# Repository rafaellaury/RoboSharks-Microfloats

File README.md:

# RoboSharks - MicroFloats

Welcome to the Team RoboSharks MicroFloats Github page. I hope you enjoy your stay!

MicroFloats is a project that aims to develop a swarm of autonomous underwater vehicles for ocean exploration. The current mission it is being developed for is the discovery of larval dispersion. Scientists in Stellwagen Bank, MA are researching this unknown phenomena, and the MicroFloats will greatly aid this scientific discovery effort.

MicroFloats is an ongoing project at Georgia Tech and has had several iterations of Senior Design teams and VIP teams working on it, hence the somewhat disorganized and multilayered structure. The VIP team has a helpful wiki that helps to explain some of the electronics and BMS specifics (link [here](https://github.gatech.edu/mwoodward6/LagrangianProfiler/wiki)!)

Check out our [website](https://eceseniordesign2022spring.ece.gatech.edu/sd22p17/) for more documentation and information about the project! The details of the github are explained below.

## CAD Models

This folder contains all of the CAD models in .SLDPRT format, and were created in SolidWorks. Details on measurements can be found in the fabrication package on our website.

## MatLab Simulations

This folder contains MatLab simulations done for the Power subsystem and antenna range. These give rough metrics for how the MicrFloat will perform since we were not able to test it in full operation.

## PCB

The PCB folder contains three subfolders, one for the Battery Management System (BMS), one for the Sensor Board, and one for the Contorl Board. These all have the most up to date KiCAD PCB schematics and board layouts in there. They also include the latest Gerber and Drill files for assembly, but it is RECOMMENDED to run a DRC again before using these pregenerated files...maybe we missed something!

## Test Code

This folder contains all the code needed to test the MicroFloat and the Sensor board in particular. 

### MicroFloat Test Code

The Arduino test Code for the whole MicroFloat came mostly from the previous team (RUR) and was adapted for our needs. Note: these files are for use with the current electronics prototyping setup, which uses an SAMD51 Thing Plus. You will have to configure your Arduino IDE to interface with this board correctly as described [here.](https://learn.sparkfun.com/tutorials/samd51-thing-plus-hookup-guide/uf2-bootloader--drivers)

The following is the documentation on each of the methods for the MicroFloats test code, taken from RUR's documentation.

The following is a brief overview and description of each test code found in the MicroFloat-Test repository. Most of the code listed is for priming the system and making sure that enough oil is in the bellows versus the reservoir to achieve neutral buoyancy. When using the following programs to calibrate oil levels, it is recommended that the electronics are off to the side so that the cap of the reservoir can be taken off, and the oil levels can be monitored. Watching the oil levels is crucial as contracting or expanding the bellows too much could cause it to pop, and expanding the bellows beyond the amount of oil in the reservoir introduces air to the system. 

*do_nothing*

This program will do as it is called, nothing. This program was written in order to test the float underwater to check neutral buoyancy. It is necessary simply because the power switch at the top of the float needs to be screwed in (and therefore the system is powered). This program ensures that the microcontroller does not send any commands. 

*full_contract*

This program will remove all oil from the bellows and into the reservoir. This would be used if trying to readjust the timings if the oil levels in the reservoir/bellows became inconsistent. This program will run once.

*full_expand*

This program will remove all the oil from the reservoir and into the bellows. This would also be used to readjust the timings if the oil levels in the reservoir/bellows became inconsistent. This program will run once.

*half_contract*

This code will remove half of the oil from the bellows, into the reservoir. This code would be run if the bellows was fully expanded with oil, and the desired state was only half expanded with oil. In this case, the float would then be at neutral buoyancy. This program will run once.

*half_expand*

This code will add half the oil from the reservoir into the bellows. This could be run if the bellows was fully contracted and the desired state was half expanded with oil. In this case, the float would then be at neutral buoyancy. This program will run once. 

*mission*

This is code to be run in a test environment. The code assumes that the starting state is with a  half contract/half expanded bellows (neutral buoyancy). It will then sink the bottom of a pool by half contracting the bellows (resulting in no oil in the bellows). It will then expand half way and wait at the bottom of the pool. The float will then expand the bellows the rest of the way to rise, and then half contract the bellows to reach neutral buoyancy again. This program runs in a loop.

### Sensor Board Test Code

The Sensor Board testing setup is described in the Final Report. Basically, it uses an ARM mbed microcontroller (hence the mbed C++ code) to send RS-232 signals to the Sensor Board, and then reads the I2C output from the Sensor Board using an Arduino. The mbed code needs to be flashed onto the mbed, and then the computer needs to be connected to the Arduino so that the serial monitor can be read to see the I2C addresses and data. The **I2C Demo** code finds the I2C addresses that are currently responding. The other programs can be used to try to get data from the Sensor Board.

## VIP Team Files

This folder contains all the VIP files at the time of our project. This could be used, but it would be better to check on the latest status on the [VIP's actual Github page](https://github.gatech.edu/Aquabots-VIP), where they have links to various useful repositories.

Have fun!

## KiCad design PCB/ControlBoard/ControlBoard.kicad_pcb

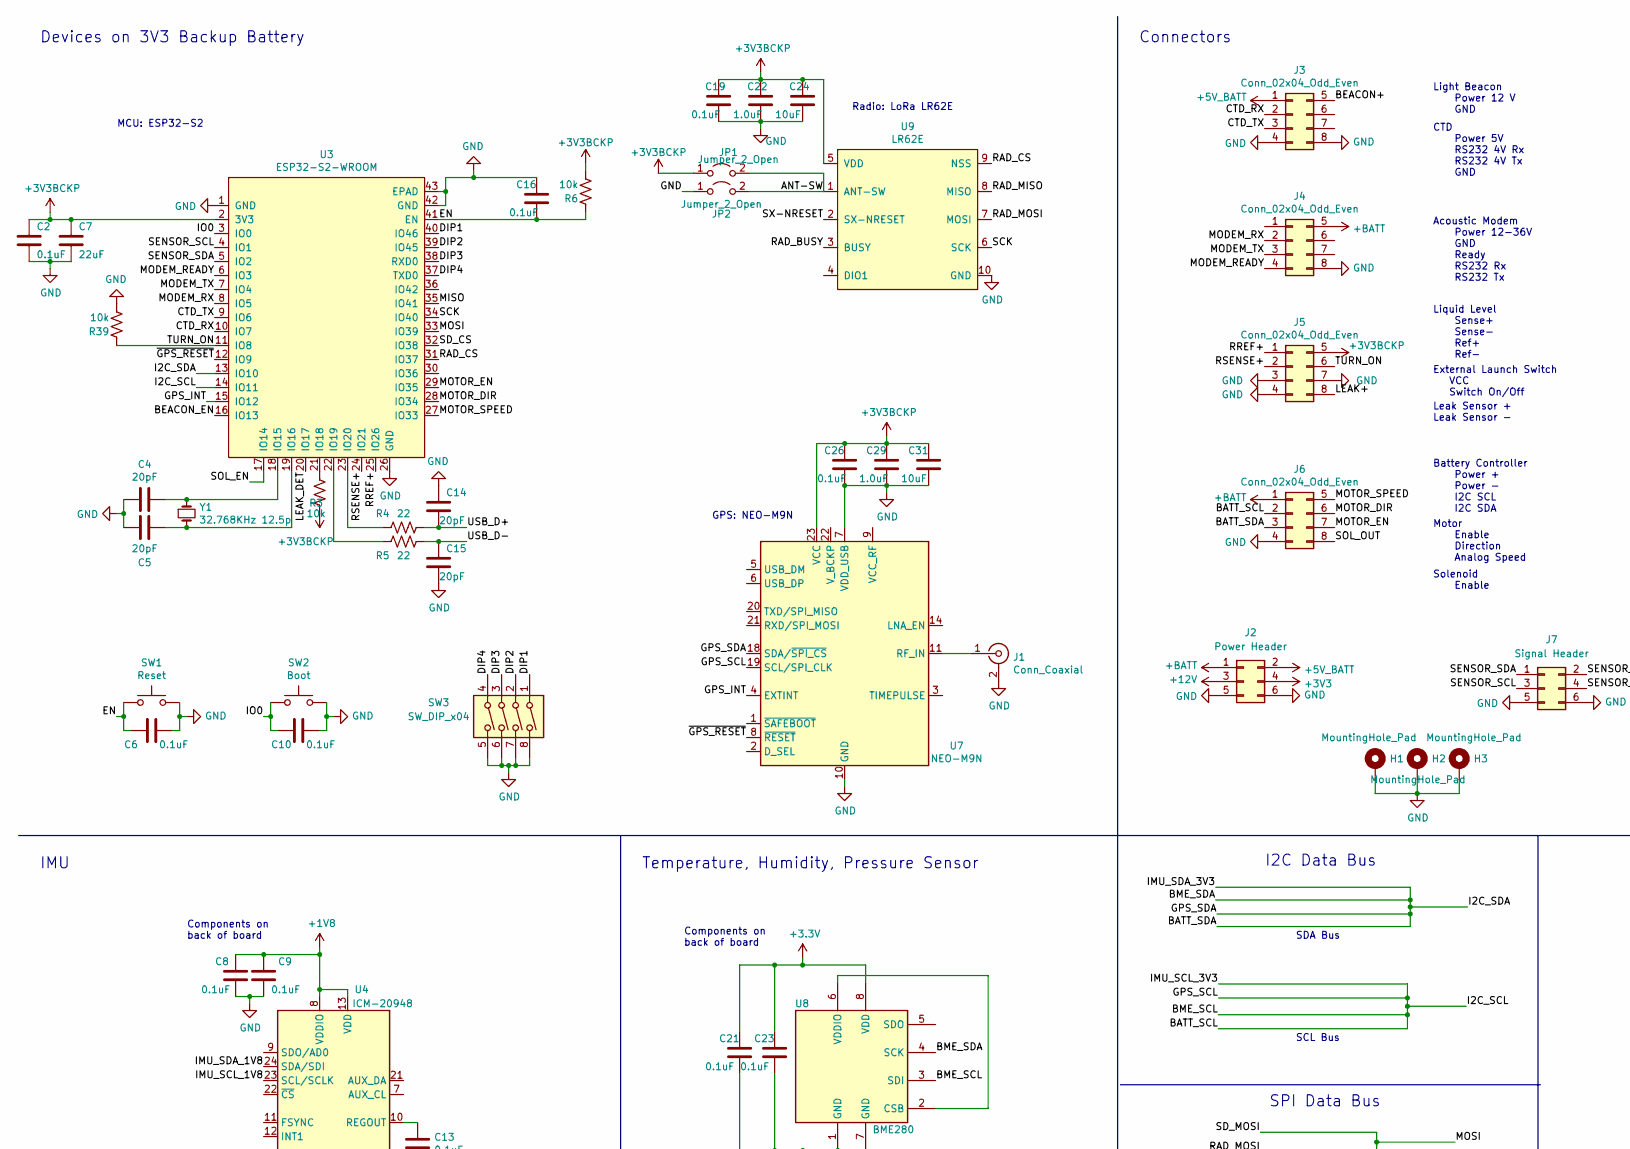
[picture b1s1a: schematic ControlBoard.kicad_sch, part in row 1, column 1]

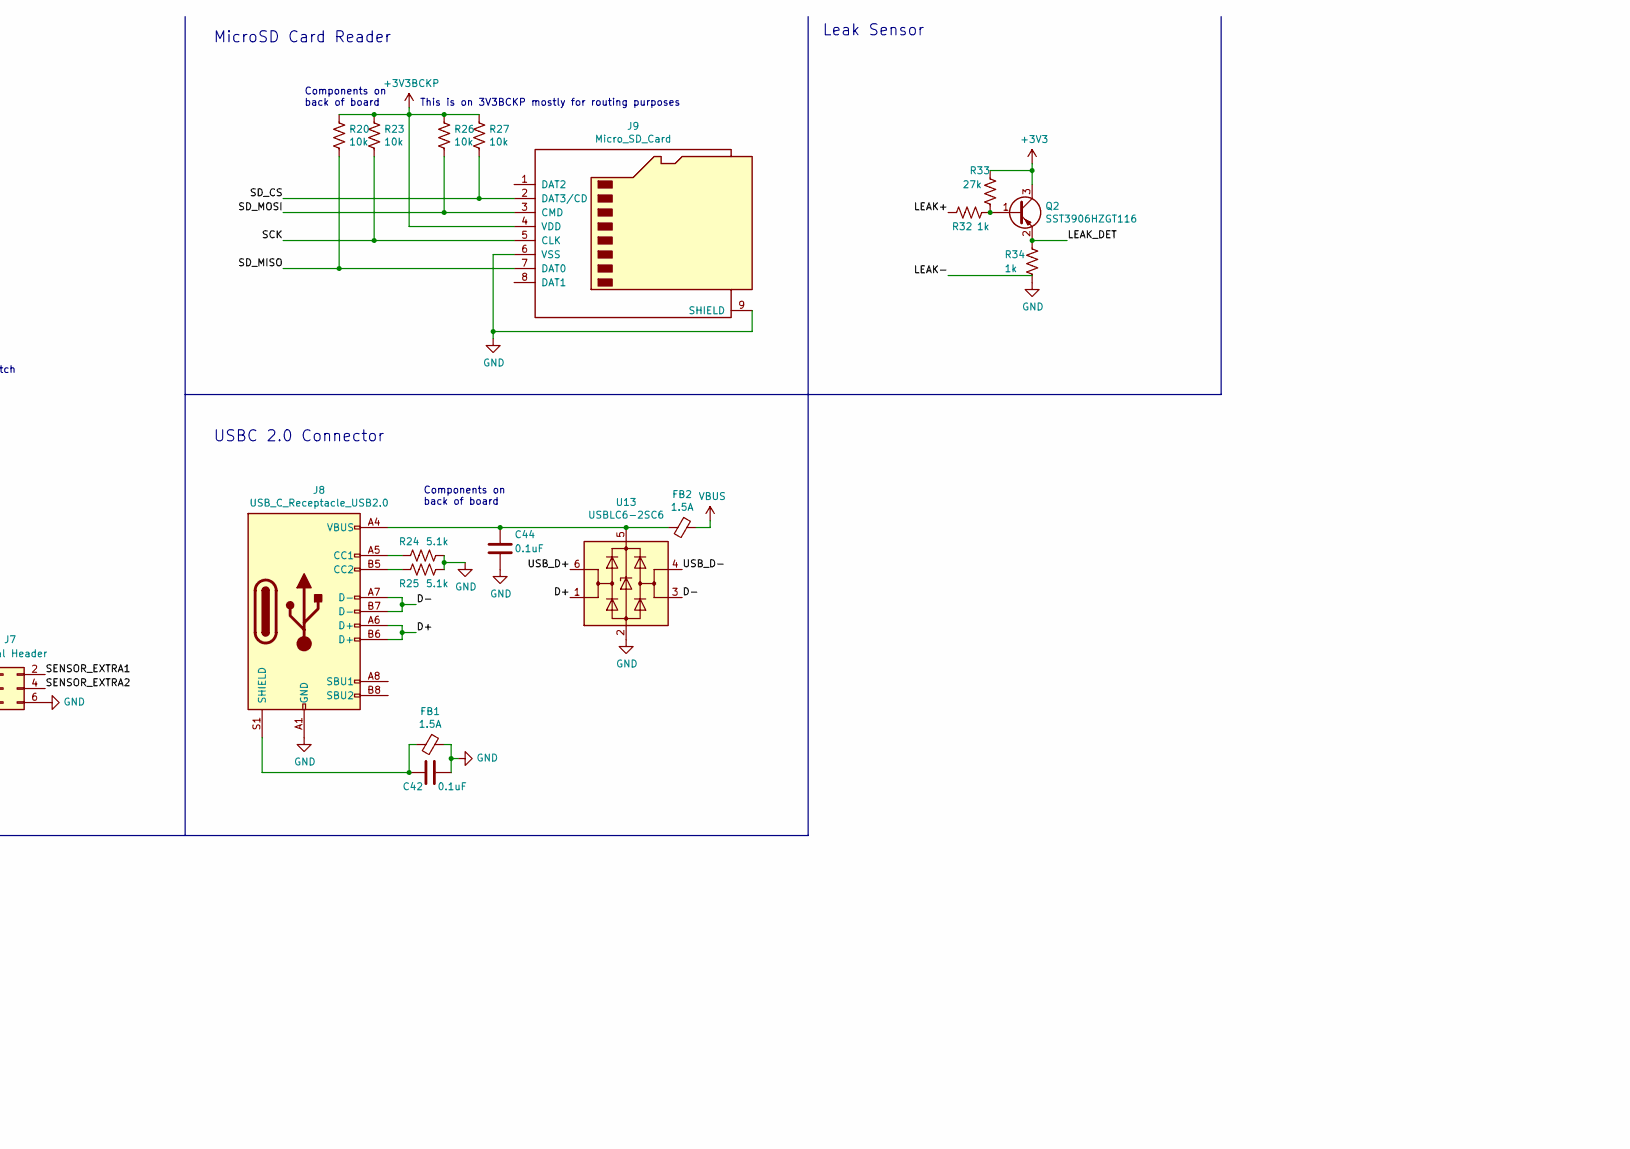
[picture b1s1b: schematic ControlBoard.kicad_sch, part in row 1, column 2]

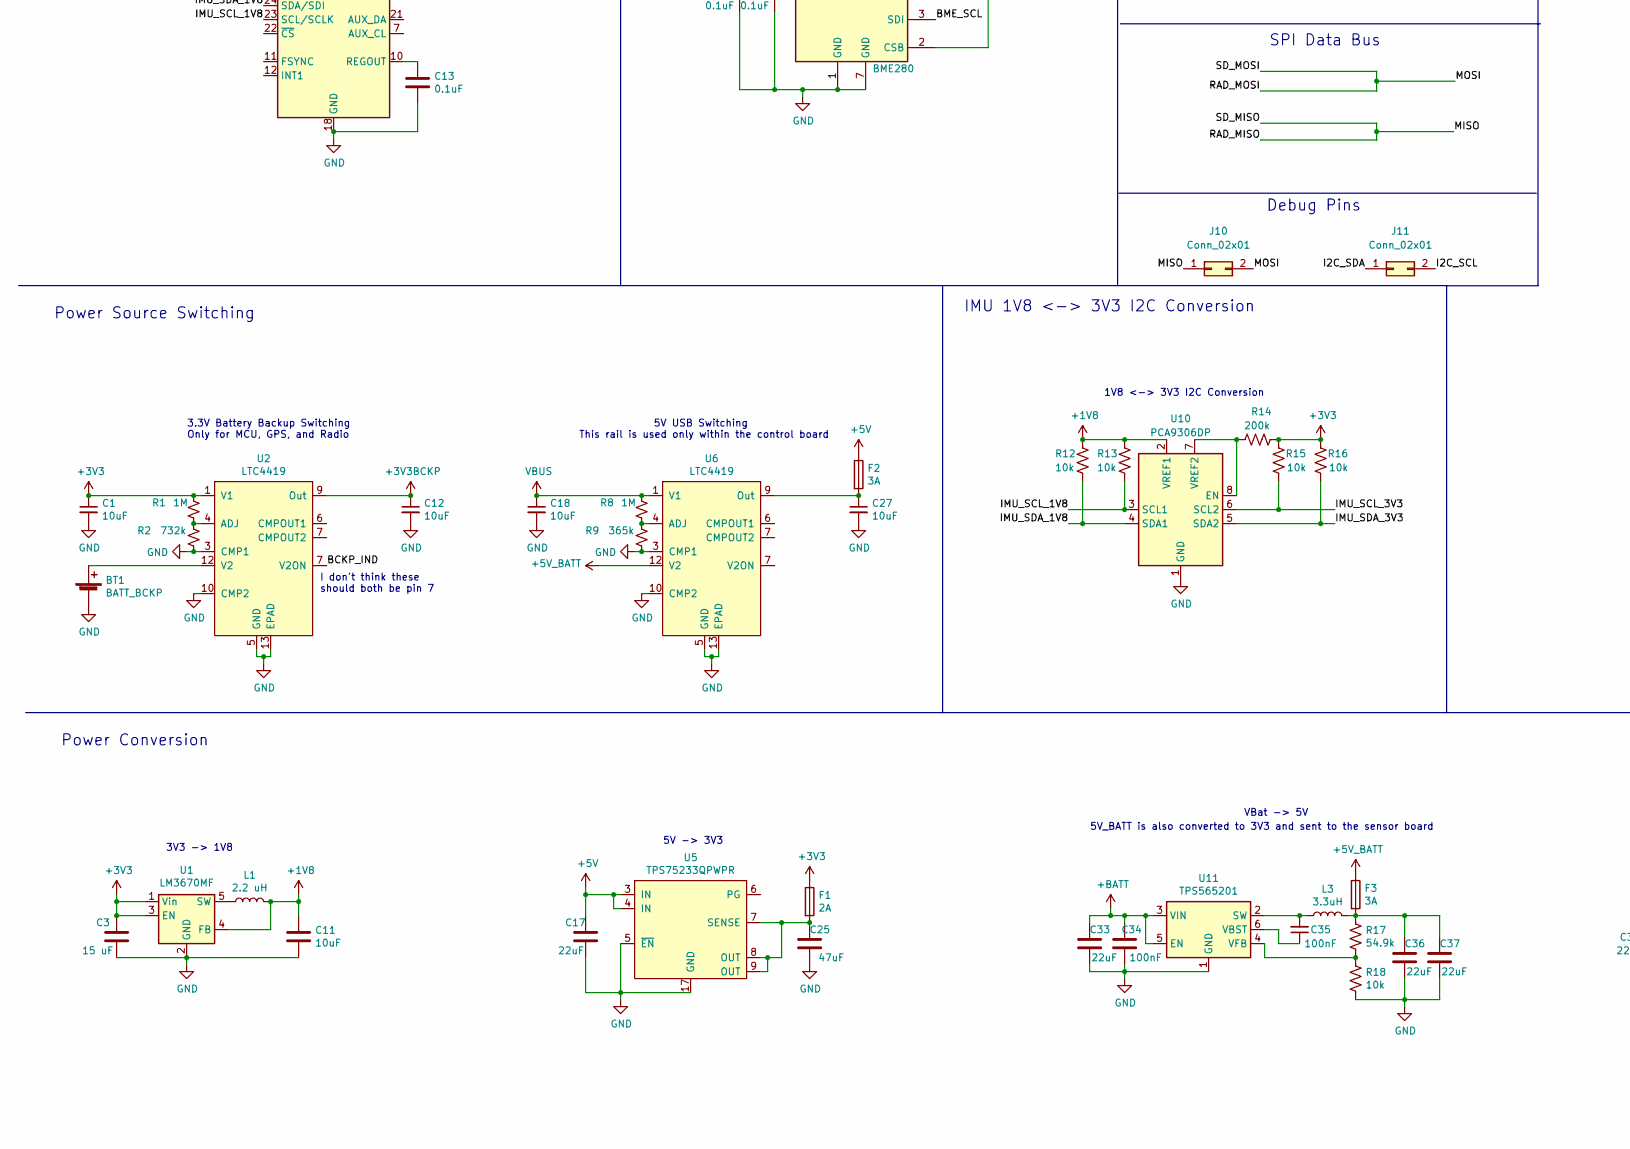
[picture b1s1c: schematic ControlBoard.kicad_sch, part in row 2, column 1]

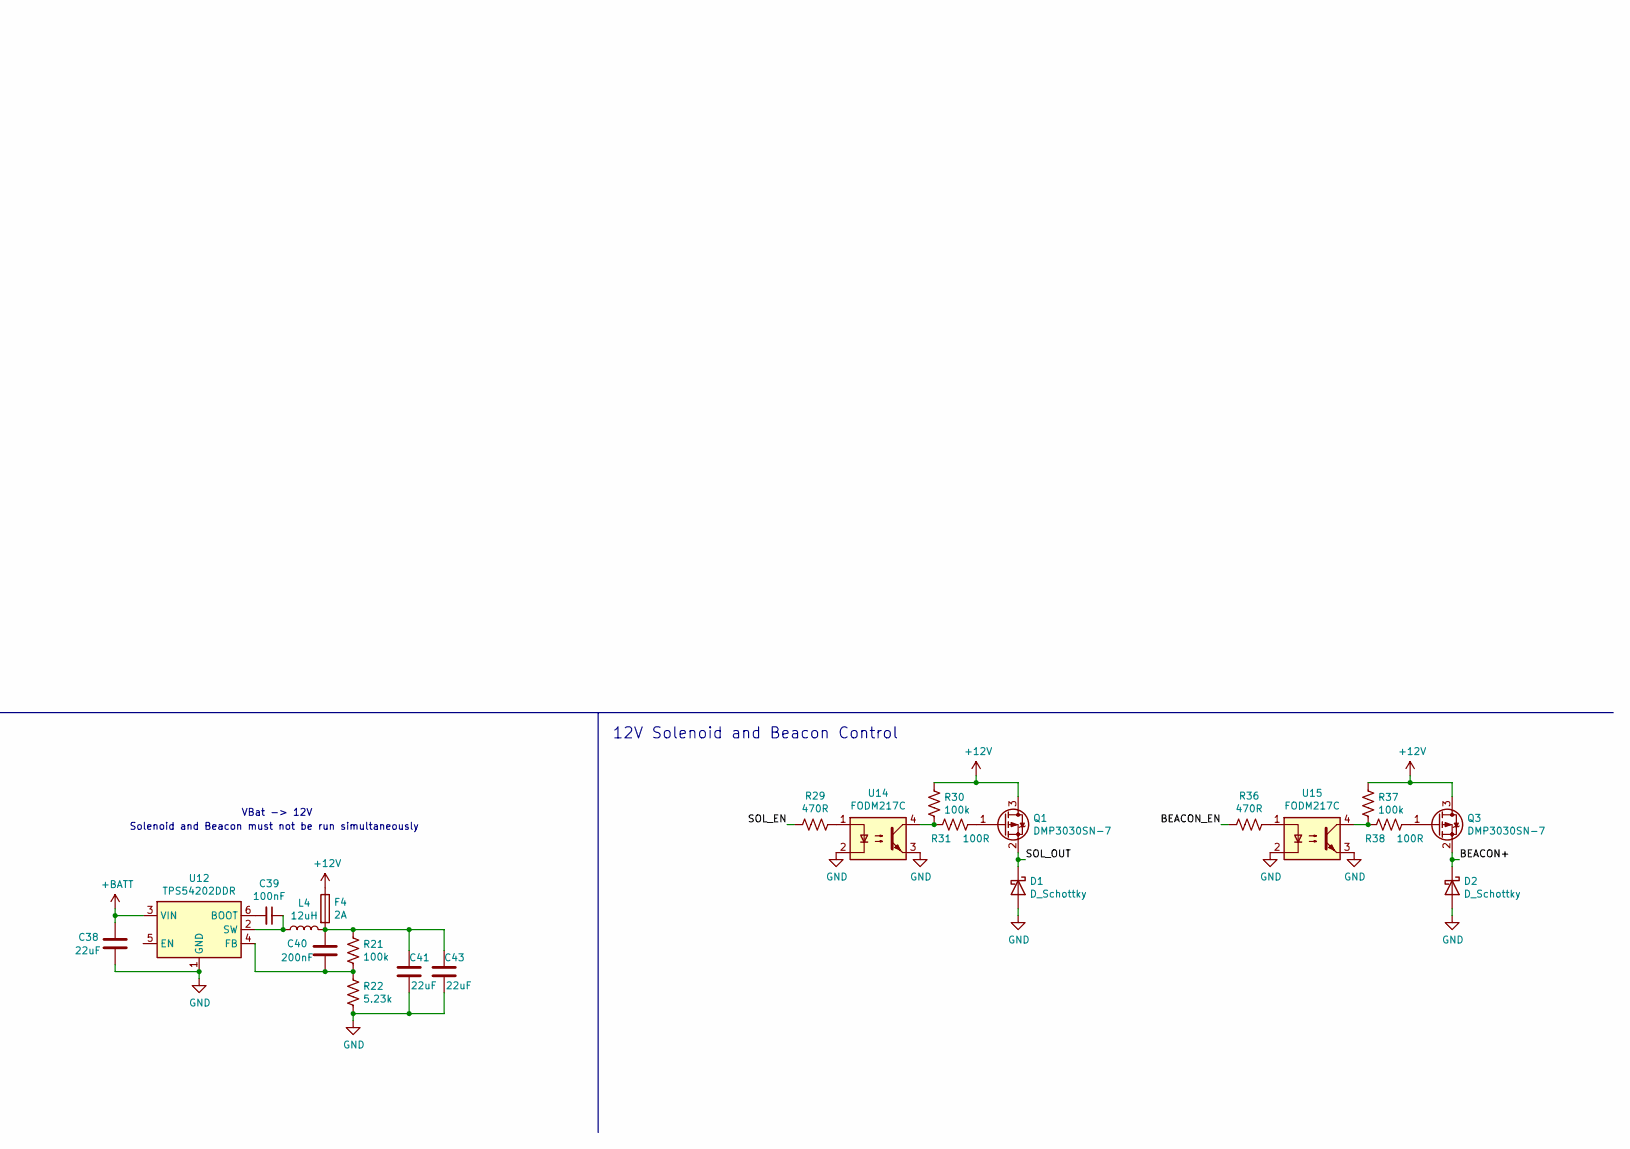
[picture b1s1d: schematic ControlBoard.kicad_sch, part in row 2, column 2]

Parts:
BT1: BATT_BCKP; BatteryHolder_Keystone_3000_1x12mm
C1, C11, C12, C18, C24, C27, C31: 10uF; C_0603_1608Metric
C2, C6, C8, C9, C10, C13, C16, C19, C21, C23, C26, C42, C44: 0.1uF; C_0603_1608Metric
C3: 15 uF; C_0603_1608Metric
C4, C5, C14, C15: 20pF; C_0603_1608Metric
C7: 22uF; C_0603_1608Metric
C17, C33, C36, C37, C38: 22uF; C_1206_3216Metric
C22, C29: 1.0uF; C_0603_1608Metric
C25: 47uF; C_1206_3216Metric
C34, C35, C39: 100nF; C_0603_1608Metric
C40: 200nF; C_0805_2012Metric
C41, C43: 22uF; CAPC6153X670N
D1, D2: D_Schottky; D_0603_1608Metric
F1, F4: 2A; Fuse_0603_1608Metric
F2, F3: 3A; Fuse_0603_1608Metric
FB1, FB2: 1.5A; L_0603_1608Metric
H1, H2, H3: MountingHole_Pad; MountingHole_3.2mm_M3_Pad_Via
J1: Conn_Coaxial; U.FL_Hirose_U.FL-R-SMT-1_Vertical
J2: Power Header; PinHeader_2x03_P2.54mm_Vertical
J3, J4, J5, J6: Conn_02x04_Odd_Even; Molex_Nano-Fit_105314-xx08_2x04_P2.50mm_Horizontal
J7: Signal Header; PinHeader_2x03_P2.54mm_Vertical
J8: USB_C_Receptacle_USB2.0; USB_C_Receptacle_HRO_TYPE-C-31-M-12
J9: Micro_SD_Card; microSD_HC_Wuerth_693072010801
J10, J11: Conn_02x01; PinHeader_2x01_P2.54mm_Vertical
JP1, JP2: Jumper_2_Open; SolderJumper-2_P1.3mm_Open_Pad1.0x1.5mm
L1: 2.2 uH; L_0805_2012Metric
L3: 3.3uH; Vishay-IHLP-3232DZ-FP_2.413x5.334-3D_4.0-0-0-MFG
L4: 12uH; L_Wuerth_WE-LQS-8040
Q1, Q3: DMP3030SN-7; SOT-23
Q2: SST3906HZGT116; SOT-23
R1, R8: 1M; R_0603_1608Metric
R2: 732k; R_0603_1608Metric
R3, R6, R12, R13, R15, R16, R18, R20, R23, R26, R27, R39: 10k; R_0603_1608Metric
R4, R5: 22; R_0603_1608Metric
R9: 365k; R_0603_1608Metric
R14: 200k; R_0603_1608Metric
R17: 54.9k; R_0603_1608Metric
R21, R30, R37: 100k; R_0603_1608Metric
R22: 5.23k; R_0603_1608Metric
R24, R25: 5.1k; R_0603_1608Metric
R29, R36: 470R; R_0603_1608Metric
R31, R38: 100R; R_0603_1608Metric
R32, R34: 1k; R_0603_1608Metric
R33: 27k; R_0603_1608Metric
SW1: Reset; SW_Push_SPST_NO_Alps_SKRK
SW2: Boot; SW_Push_SPST_NO_Alps_SKRK
SW3: SW_DIP_x04; SW_DIP_SPSTx04_Slide_6.7x11.72mm_W8.61mm_P2.54mm_LowProfile
U1: LM3670MF; TSOT-23-5
U2, U6: LTC4419; MSOP-12-1EP_3x4mm_P0.65mm_EP1.65x2.85mm_ThermalVias
U3: ESP32-S2-WROOM
U4: ICM-20948; InvenSense_QFN-24_3x3mm_P0.4mm
U5: TPS75233QPWPR; SOP65P640X110-21N
U7: NEO-M9N; ublox_NEO
U8: BME280; Bosch_LGA-8_2.5x2.5mm_P0.65mm_ClockwisePinNumbering
U9: LR62E
U10: PCA9306DP; TSSOP-8_3x3mm_P0.65mm
U11: TPS565201; SOT-23-6
U12: TPS54202DDR; SOT-23-6
U13: USBLC6-2SC6; SOT-23-6
U14, U15: FODM217C; SOP-4_4.4x2.6mm_P1.27mm
Y1: 32.768KHz 12.5p; Crystal_SMD_3215-2Pin_3.2x1.5mm

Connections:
+1V8: C8.1, C9.1, C11.1, L1.2, R12.2, R13.2, U1.4 (FB), U4.8 (VDDIO), U4.13 (VDD), U10.2 (VREF1)
+3.3BCKP: C2.1, C7.1, C12.1, C19.1, C22.1, C24.1, C26.1, C29.1, C31.1, J5.5, J9.4 (VDD), JP1.1 (A), R3.2, R6.2, R20.1, R23.1, R26.1, R27.1, U2.9 (Out), U3.2 (3V3), U7.23 (VCC), U9.5 (VDD)
+5V: C17.1, F2.1, U5.3 (IN), U5.4 (IN)
+5_BATT: F3.1, J2.2, J3.1, U6.12 (V2)
+12V: F4.1, J2.3, Q1.3 (D), Q3.3 (D), R30.1, R37.1
+BATT: C33.2, C34.2, C38.2, J2.1, J4.5, J6.1, U11.3 (VIN), U11.5 (EN), U12.3 (VIN)
/ANT-SW: JP1.2 (B), JP2.2 (B), U9.1 (ANT-SW)
/BATT_SCL: J6.2, J11.2, R15.2, U3.14 (IO11), U7.19 (SCL/SPI_CLK), U8.3 (SDI), U10.6 (SCL2)
/BATT_SDA: J6.3, J11.1, R16.2, U3.13 (IO10), U7.18 (SDA/~SPI_CS), U8.4 (SCK), U10.5 (SDA2)
/BCKP_IND: U2.7 (V2ON)
/BEACON+: D2.1 (K), J3.5, Q3.2 (S)
/BEACON_EN: R36.2, U3.16 (IO13)
/CTD_RX: J3.2, U3.10 (IO7)
/CTD_TX: J3.3, U3.9 (IO6)
/D+: J8.A6 (D+), J8.B6 (D+), U13.1 (I/O1)
/D-: J8.A7 (D-), J8.B7 (D-), U13.3 (I/O2)
/DIP1: SW3.1, U3.40 (IO46)
/DIP2: SW3.2, U3.39 (IO45)
/DIP3: SW3.3, U3.38 (RXD0)
/DIP4: SW3.4, U3.37 (TXD0)
/EN: C6.2, C16.2, R6.1, SW1.1, U3.41 (EN)
/GPS_INT: U3.15 (IO12), U7.4 (EXTINT)
/IMU_SCL_1V8: R13.1, U4.23 (SCL/SCLK), U10.3 (SCL1)
/IMU_SDA_1V8: R12.1, U4.24 (SDA/SDI), U10.4 (SDA1)
/IO0: C10.2, SW2.1, U3.3 (IO0)
/LEAK+: J5.8, R32.2
/LEAK_DET: Q2.2 (E), R34.2, U3.20 (IO17)
/MISO: J9.7 (DAT0), J10.1, R20.2, U3.35 (IO41), U9.8 (MISO)
/MODEM_READY: J4.4, U3.6 (IO3)
/MODEM_RX: J4.2, U3.8 (IO5)
/MODEM_TX: J4.3, U3.7 (IO4)
/MOSI: J9.3 (CMD), J10.2, R26.2, U3.33 (IO39), U9.7 (MOSI)
/MOTOR_DIR: J6.6, U3.28 (IO34)
/MOTOR_EN: J6.7, U3.29 (IO35)
/MOTOR_SPEED: J6.5, U3.27 (IO33)
/RAD_BUSY: U9.3 (BUSY)
/RAD_CS: U3.31 (IO37), U9.9 (NSS)
/RREF+: J5.1, U3.25 (IO26)
/RSENSE+: J5.2, U3.24 (IO21)
/SCK: J9.5 (CLK), R23.2, U3.34 (IO40), U9.6 (SCK)
/SD_CS: J9.2 (DAT3/CD), R27.2, U3.32 (IO38)
/SENSOR_EXTRA1: J7.2
/SENSOR_EXTRA2: J7.4
/SENSOR_SCL: J7.3, U3.4 (IO1)
/SENSOR_SDA: J7.1, U3.5 (IO2)
/SOL_EN: R29.2, U3.17 (IO14)
/SOL_OUT: D1.1 (K), J6.8, Q1.2 (S)
/SX-NRESET: U9.2 (SX-NRESET)
/TURN_ON: J5.6, R39.1, U3.11 (IO8)
/USB_D+: C14.2, R4.2, U13.6 (I/O1)
/USB_D-: C15.1, R5.2, U13.4 (I/O2)
/~GPS_RESET: U3.12 (IO9), U7.8 (~RESET)
GND: BT1.2 (-), C1.2, C2.2, C3.1, C4.2, C5.1, C6.1, C7.2, C8.2, C9.2, C10.1, C11.2, C12.2, C13.2, C14.1, C15.2, C16.1, C17.2, C18.2, C19.2, C21.2, C22.2, C23.2, C24.2, C25.1, C26.2, C27.2, C29.2, C31.2, C33.1, C34.1, C36.1, C37.1, C38.1, C41.1, C42.1, C43.1, C44.2, D1.2 (A), D2.2 (A), FB1.1, H1.1, H2.1, H3.1, J1.2 (Ext), J2.5, J2.6, J3.4, J3.8, J4.8, J5.3, J5.4, J5.7, J6.4, J7.5, J7.6, J8.A1 (GND), J8.A12 (GND), J8.B1 (GND), J8.B12 (GND), J9.6 (VSS), J9.9 (SHIELD), JP2.1 (A), R2.1, R9.1, R18.1, R22.1, R24.2, R25.1, R34.1, R39.2, SW1.2, SW2.2, SW3.5, SW3.6, SW3.7, SW3.8, U1.2 (GND), U2.3 (CMP1), U2.5 (GND), U2.10 (CMP2), U2.13 (EPAD), U3.1 (GND), U3.26 (GND), U3.42 (GND), U3.43 (EPAD), U4.18 (GND), U4.20 (GND), U5.5 (~EN), U5.17 (GND), U6.3 (CMP1), U6.5 (GND), U6.10 (CMP2), U6.13 (EPAD), U7.7 (VDD_USB), U7.10 (GND), U7.12 (GND), U7.13 (GND), U7.24 (GND), U8.1 (GND), U8.7 (GND), U9.10 (GND), U10.1 (GND), U11.1 (GND), U12.1 (GND), U13.2 (GND), U14.2, U14.3, U15.2, U15.3
unnamed: BT1.1 (+), U2.12 (V2)
unnamed: C4.1, U3.18 (IO15), Y1.1
unnamed: C5.2, U3.19 (IO16), Y1.2
unnamed: C13.1, U4.10 (REGOUT)
unnamed: C25.2, F1.2, U5.7 (SENSE), U5.8 (OUT), U5.9 (OUT)
unnamed: C27.1, F2.2, U6.9 (Out)
unnamed: C35.1, U11.6 (VBST)
unnamed: C35.2, L3.1, U11.2 (SW)
unnamed: C36.2, C37.2, F3.2, L3.2, R17.1
unnamed: C39.1, L4.1, U12.2 (SW)
unnamed: C39.2, U12.6 (BOOT)
unnamed: C40.1, C41.2, C43.2, F4.2, L4.2, R21.1
unnamed: C40.2, R21.2, R22.2, U12.4 (FB)
unnamed: C42.2, FB1.2, J8.S1 (SHIELD)
unnamed: C44.1, FB2.2, J8.A4 (VBUS), J8.A9 (VBUS), J8.B4 (VBUS), J8.B9 (VBUS), U13.5 (VBUS)
unnamed: J1.1 (In), U7.11 (RF_IN)
unnamed: J8.A5 (CC1), R24.1
unnamed: J8.B5 (CC2), R25.2
unnamed: L1.1, U1.5 (SW)
unnamed: Q1.1 (G), R31.1
unnamed: Q2.1 (B), R32.1, R33.1
unnamed: Q3.1 (G), R38.1
unnamed: R1.2, R2.2, U2.4 (ADJ)
unnamed: R3.1, U3.21 (IO18)
unnamed: R4.1, U3.23 (IO20)
unnamed: R5.1, U3.22 (IO19)
unnamed: R8.2, R9.2, U6.4 (ADJ)
unnamed: R14.1, U10.7 (VREF2), U10.8 (EN)
unnamed: R17.2, R18.2, U11.4 (VFB)
unnamed: R29.1, U14.1
unnamed: R30.2, R31.2, U14.4
unnamed: R36.1, U15.1
unnamed: R37.2, R38.2, U15.4
unnamed: U8.2 (CSB), U8.6 (VDDIO)
VBUS: C18.1, FB2.1, R8.1, U6.1 (V1)

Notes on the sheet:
External Launch Switch VCC Switch On/Off
I2C Data Bus
Components on back of board
SCL Bus
Devices on 3V3 Backup Battery
USBC 2.0 Connector
Power Source Switching
I don't think these should both be pin 7
Light Beacon Power 12 V GND
Battery Controller Power + Power - I2C SCL I2C SDA
1V8 <-> 3V3 I2C Conversion
Leak Sensor
Power Conversion
Debug Pins
Connectors
Motor Enable Direction Analog Speed
Acoustic Modem Power 12-36V GND Ready RS232 Rx RS232 Tx
GPS: NEO-M9N
5V_BATT is also converted to 3V3 and sent to the sensor board
Leak Sensor + Leak Sensor -
SPI Data Bus
IMU
This is on 3V3BCKP mostly for routing purposes
Temperature, Humidity, Pressure Sensor
12V Solenoid and Beacon Control
3.3V Battery Backup Switching Only for MCU, GPS, and Radio
Solenoid Enable
Liquid Level Sense+ Sense- Ref+ Ref-
Radio: LoRa LR62E
3V3 -> 1V8
MCU: ESP32-S2
5V -> 3V3
CTD Power 5V RS232 4V Rx RS232 4V Tx GND
MicroSD Card Reader
VBat -> 12V
IMU 1V8 <-> 3V3 I2C Conversion
VBat -> 5V
Solenoid and Beacon must not be run simultaneously
5V USB Switching This rail is used only within the control board
SDA Bus

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
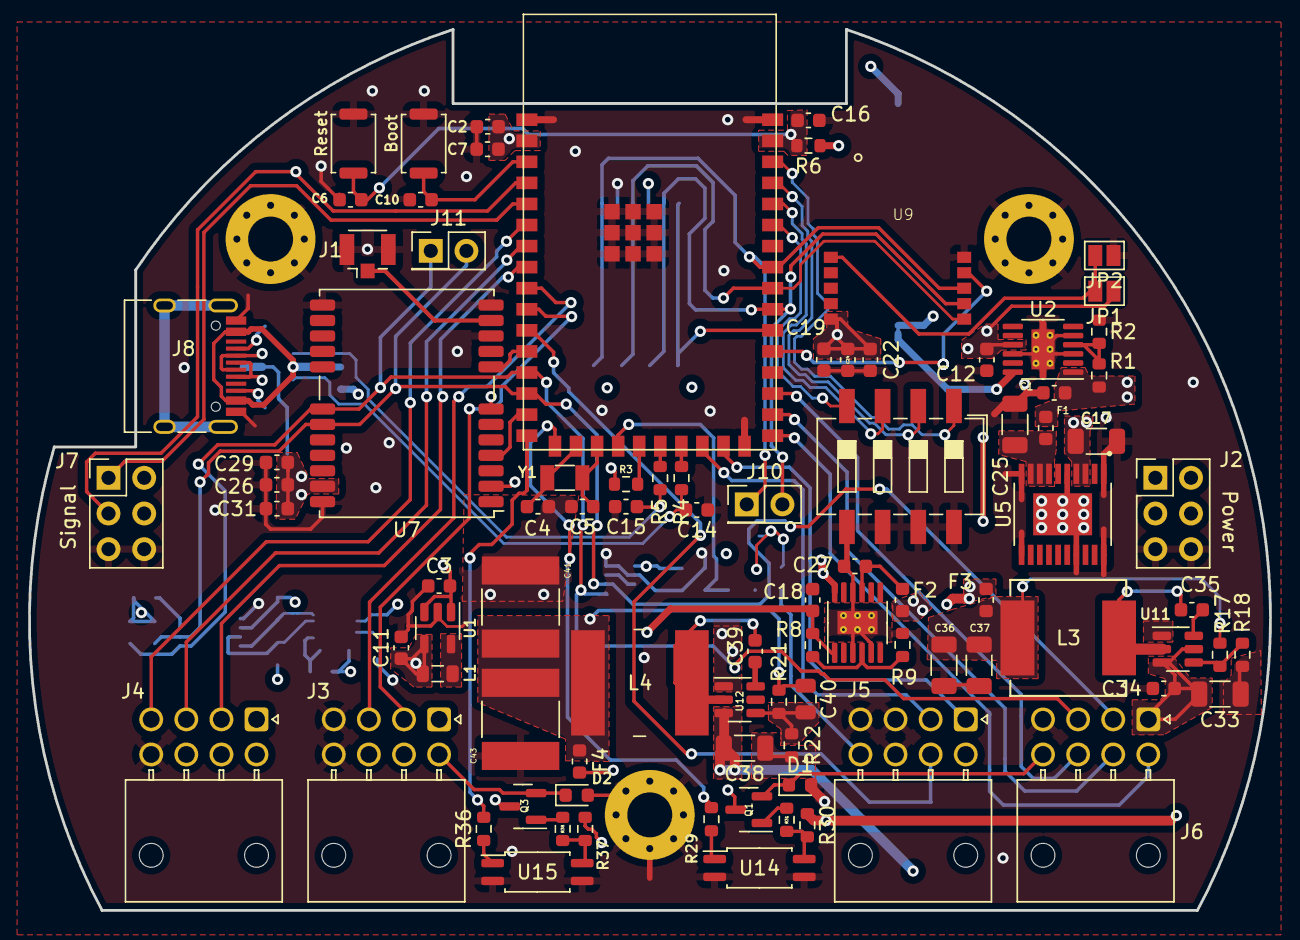
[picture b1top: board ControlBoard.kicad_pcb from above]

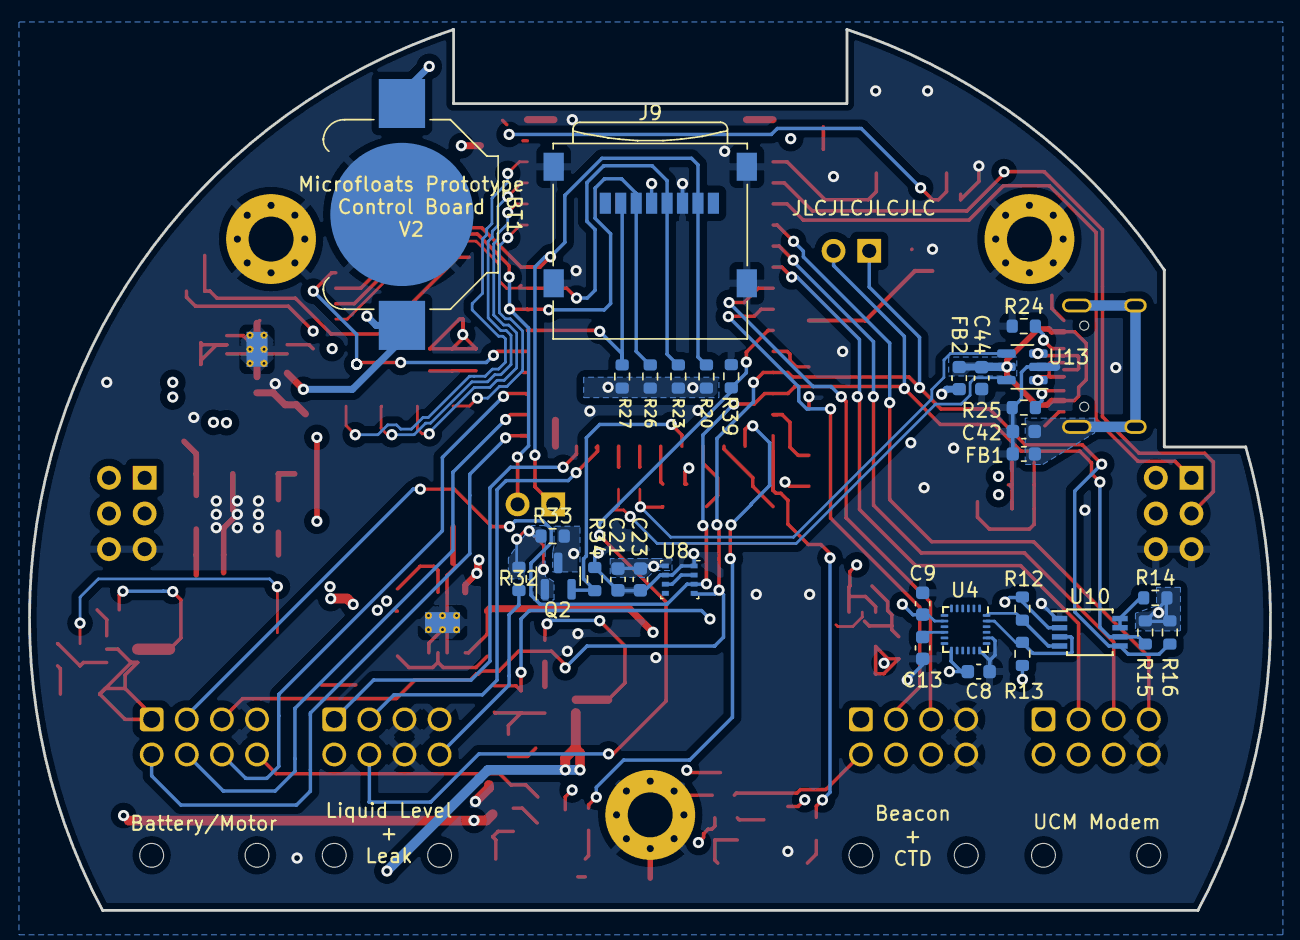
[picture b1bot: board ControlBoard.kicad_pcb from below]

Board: 4 copper layers, 88.4 x 62.7 mm, 123 parts (31 on the bottom side), 84 nets.

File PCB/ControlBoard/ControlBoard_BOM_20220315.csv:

"Id";"Designator";"Package";"Quantity";"Designation";"Supplier and ref";
1;"U5";"SOP65P640X110-21N";1;"TPS75233QPWPR";;;
2;"J8";"USB_C_Receptacle_HRO_TYPE-C-31-M-12";1;"USB_C_Receptacle_USB2.0";;;
3;"J3,J4,J5,J6";"Molex_Nano-Fit_105314-xx08_2x04_P2.50mm_Horizontal";4;"Conn_02x04_Odd_Even";;;
4;"U7";"ublox_NEO";1;"NEO-M9N";;;
5;"U3";"ESP32-S2-WROOM";1;"ESP32-S2-WROOM";;;
6;"R29,R36";"R_0603_1608Metric";2;"470R";;;
7;"U14,U15";"SOP-4_4.4x2.6mm_P1.27mm";2;"FODM217C";;;
8;"R31,R38";"R_0603_1608Metric";2;"100R";;;
9;"R30,R21,R37";"R_0603_1608Metric";3;"100k";;;
10;"Q1,Q3";"SOT-23";2;"DMP3030SN-7";;;
11;"D1,D2";"D_0603_1608Metric";2;"D_Schottky";;;
12;"J2";"PinHeader_2x03_P2.54mm_Vertical";1;"Power Header";;;
13;"J7";"PinHeader_2x03_P2.54mm_Vertical";1;"Signal Header";;;
14;"BT1";"BR-1632A_HAN";1;"BATT_BCKP";;;
15;"C1,C11,C12,C18,C24,C27,C31";"C_0603_1608Metric";7;"10uF";;;
16;"C2,C6,C8,C9,C10,C13,C16,C19,C21,C23,C26,C42,C44";"C_0603_1608Metric";13;"0.1uF";;;
17;"C3";"C_0603_1608Metric";1;"15 uF";;;
18;"C4,C5,C14,C15";"C_0603_1608Metric";4;"20pF";;;
19;"C7";"C_0603_1608Metric";1;"22uF";;;
20;"C17,C33,C36,C37,C38";"C_1206_3216Metric";5;"22uF";;;
21;"C22,C29";"C_0603_1608Metric";2;"1.0uF";;;
22;"C34,C35,C39";"C_0603_1608Metric";3;"100nF";;;
23;"C40";"C_0805_2012Metric";1;"200nF";;;
24;"C41,C43";"CAPC6153X670N";2;"22uF";;;
25;"F1,F4";"Fuse_0603_1608Metric";2;"2A";;;
26;"F2,F3";"Fuse_0603_1608Metric";2;"3A";;;
27;"FB1,FB2";"L_0603_1608Metric";2;"1.5A";;;
28;"J1";"U.FL_Hirose_U.FL-R-SMT-1_Vertical";1;"Conn_Coaxial";;;
29;"J9";"microSD_HC_Wuerth_693072010801";1;"Micro_SD_Card";;;
30;"L1";"L_0805_2012Metric";1;"2.2 uH";;;
31;"L3";"Vishay-IHLP-3232DZ-FP_2.413x5.334-3D_4.0-0-0-MFG";1;"3.3uH";;;
32;"L4";"L_Wuerth_WE-LQS-8040";1;"12uH";;;
33;"Q2";"SOT-23";1;"SST3906HZGT116";;;
34;"R1,R8";"R_0603_1608Metric";2;"1M";;;
35;"R2";"R_0603_1608Metric";1;"732k";;;
36;"R3,R6,R12,R13,R15,R16,R18,R19,R20,R23,R26,R27,R28";"R_0603_1608Metric";13;"10k";;;
37;"R4,R5";"R_0603_1608Metric";2;"22";;;
38;"R9";"R_0603_1608Metric";1;"365k";;;
39;"R14";"R_0603_1608Metric";1;"200k";;;
40;"R17";"R_0603_1608Metric";1;"54.9k";;;
41;"R22";"R_0603_1608Metric";1;"5.23k";;;
42;"R24,R25";"R_0603_1608Metric";2;"5.1k";;;
43;"R32,R34";"R_0603_1608Metric";2;"1k";;;
44;"R33";"R_0603_1608Metric";1;"27k";;;
45;"SW1";"SW_Push_SPST_NO_Alps_SKRK";1;"Reset";;;
46;"SW2";"SW_Push_SPST_NO_Alps_SKRK";1;"Boot";;;
47;"SW3";"SW_DIP_SPSTx04_Slide_6.7x11.72mm_W8.61mm_P2.54mm_LowProfile";1;"SW_DIP_x04";;;
48;"U1";"TSOT-23-5";1;"LM3670MF";;;
49;"U2,U6";"MSOP-12-1EP_3x4mm_P0.65mm_EP1.65x2.85mm_ThermalVias";2;"LTC4419";;;
50;"U4";"InvenSense_QFN-24_3x3mm_P0.4mm";1;"ICM-20948";;;
51;"U8";"Bosch_LGA-8_2.5x2.5mm_P0.65mm_ClockwisePinNumbering";1;"BME280";;;
52;"U9";"LR62E";1;"LR62E";;;
53;"U10";"TSSOP-8_3x3mm_P0.65mm";1;"PCA9306DP";;;
54;"U11";"SOT-23-6";1;"TPS565201";;;
55;"U12";"SOT-23-6";1;"TPS54202DDR";;;
56;"U13";"SOT-23-6";1;"USBLC6-2SC6";;;
57;"Y1";"Crystal_SMD_3215-2Pin_3.2x1.5mm";1;"32.768KHz 12.5p";;;
58;"C25";"C_1206_3216Metric";1;"47uF";;;

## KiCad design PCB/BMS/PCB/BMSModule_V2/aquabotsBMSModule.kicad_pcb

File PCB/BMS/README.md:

# Battery Management System
For more information please check out our [wiki](https://github.gatech.edu/Aquabots-VIP/BatteryManagementSystem/wiki)!

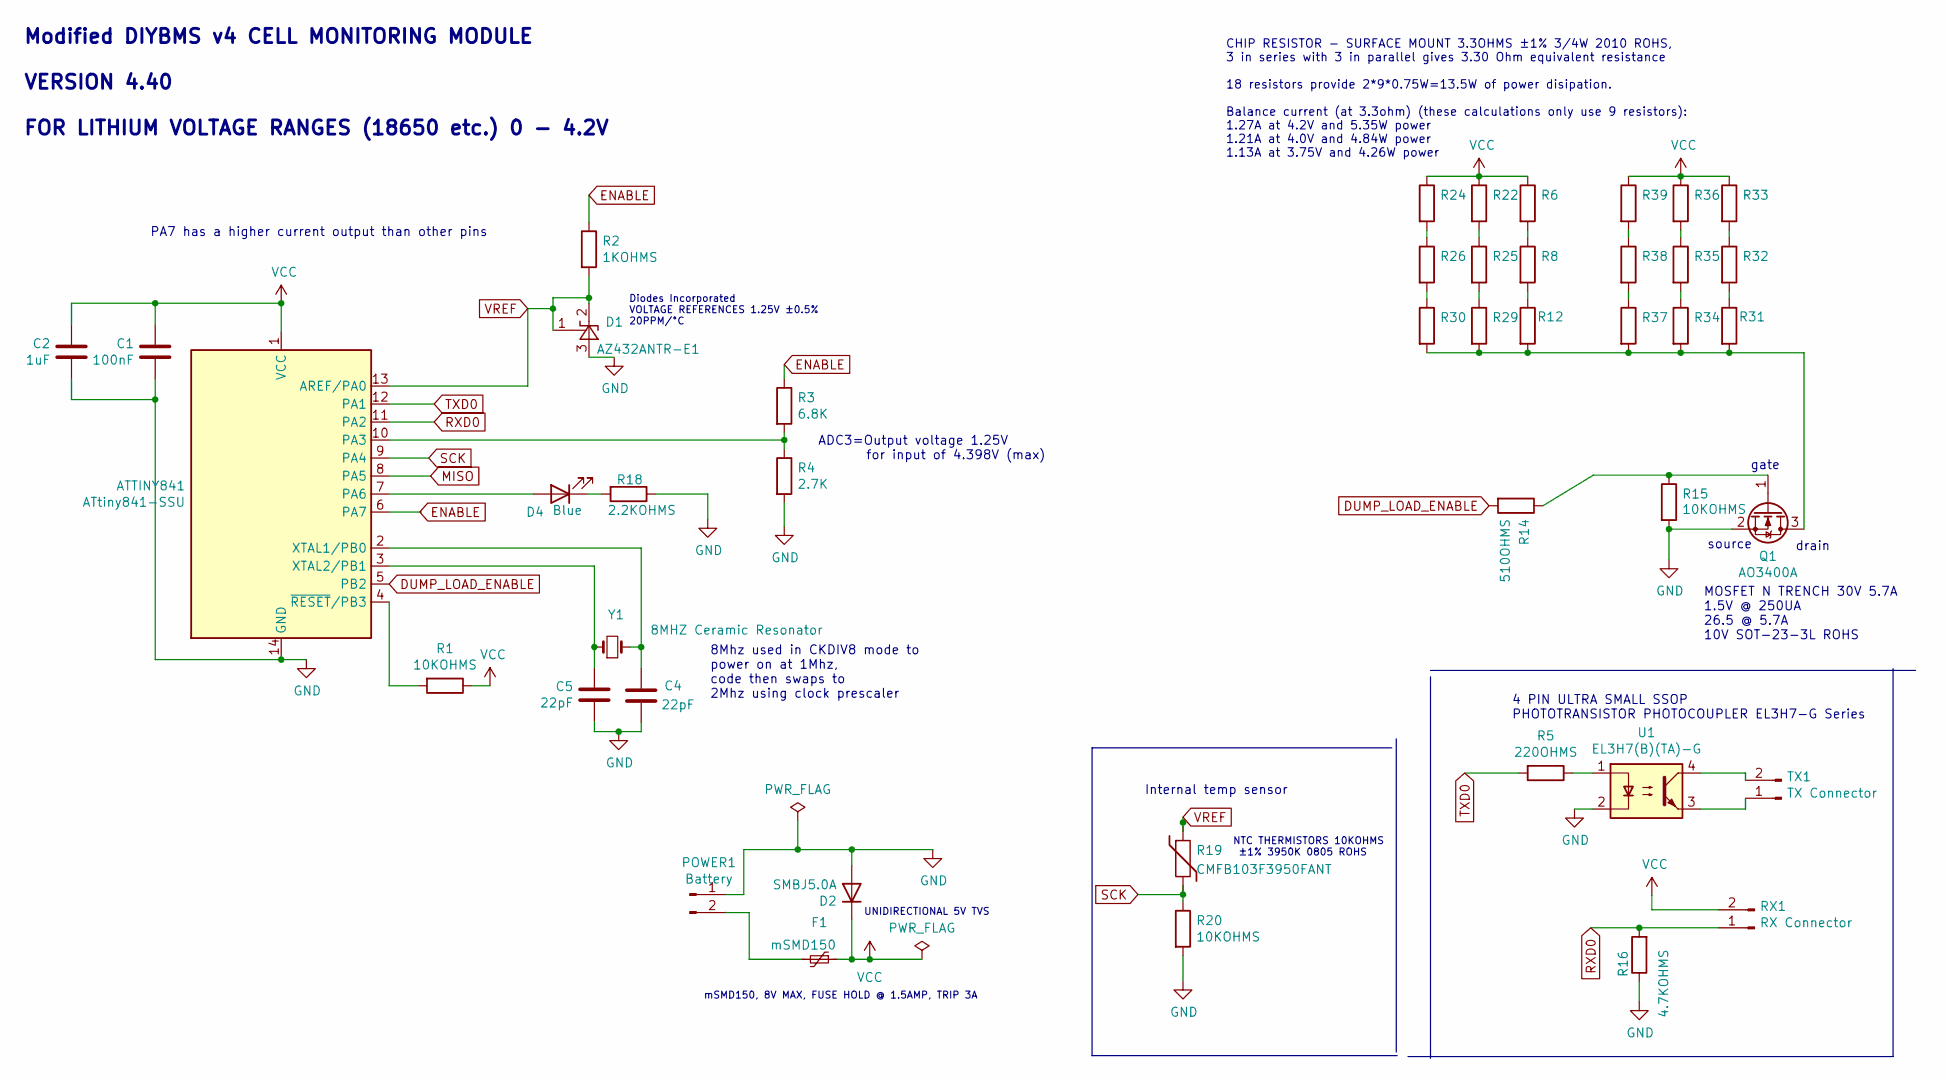
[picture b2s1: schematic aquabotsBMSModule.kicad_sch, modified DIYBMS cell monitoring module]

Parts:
ATTINY841: ATtiny841-SSU; SOIC-14_3.9x8.7mm_P1.27mm; LCSCStockCode C219103
C1: 100nF; C_0805_2012Metric; PartNumber CC0805KRX7R9BB104; LCSCStockCode C49678
C2: 1uF; C_0805_2012Metric; PartNumber CL21B105KBFNNNE; LCSCStockCode C28323
C4, C5: 22pF; C_0805_2012Metric; PartNumber CL21C220JBANNNC; LCSCStockCode C1804
D1: AZ432ANTR-E1; SOT-23; PartNumber AZ432ANTR-E1; LCSCStockCode C84139
D2: SMBJ5.0A; D_SMB; LCSCStockCode C440263
D4: Blue; LED_0805_2012Metric; PartNumber Blue LED; LCSCStockCode C2293
F1: mSMD150; Fuse_1812_4532Metric; PartNumber mSMD150; LCSCStockCode C70121
POWER1: Battery; JST_PH_S2B-PH-K_1x02_P2.00mm_Horizontal; PartNumber S2B-PH-K(LF)(SN); LCSCStockCode C265016
Q1: AO3400A; SOT-23; PartNumber AO3400A; LCSCStockCode C20917
R1, R15, R20: 10KOHMS; R_0805_2012Metric; PartNumber 0805W8F1002T5E; LCSCStockCode C17414
R2: 1KOHMS; R_0805_2012Metric; PartNumber 0805W8F1001T5E; LCSCStockCode C17513
R3: 6.8K; R_0805_2012Metric; PartNumber 0805W8F6801T5E; LCSCStockCode C17772
R4: 2.7K; R_0805_2012Metric; PartNumber 0805W8F2701T5E; LCSCStockCode C17530
R5: 220OHMS; R_0805_2012Metric; PartNumber 0805W8F2200T5E; LCSCStockCode C17557
R6, R8, R12, R22, R24, R25, R26, R29, R30, R31, R32, R33, R34, R35, R36, R37, R38, R39: 3.3OHM 3/4W; R_2010_5025Metric; PartNumber 201007F330KT4E; LCSCStockCode C270971
R14: 510OHMS; R_0805_2012Metric; PartNumber 0805W8F5100T5E; LCSCStockCode C17734
R16: 4.7KOHMS; R_0805_2012Metric; PartNumber 0805W8F4701T5E; LCSCStockCode C17673
R18: 2.2KOHMS; R_0805_2012Metric; PartNumber 0805W8F2201T5E; LCSCStockCode C17520
R19: CMFB103F3950FANT; R_0805_2012Metric; PartNumber CMFB103F3950FANT; LCSCStockCode C51597
RX1: RX Connector; JST_PH_S2B-PH-K_1x02_P2.00mm_Horizontal; PartNumber S2B-PH-K(LF)(SN); LCSCStockCode C265016
TX1: TX Connector; JST_PH_S2B-PH-K_1x02_P2.00mm_Horizontal; PartNumber S2B-PH-K(LF)(SN); LCSCStockCode C265016
U1: EL3H7(B)(TA)-G; SOP-4_4.4x2.6mm_P1.27mm; PartNumber EL3H7(B)(TA)-G; LCSCStockCode C32565
Y1: 8MHZ Ceramic Resonator; Crystal_SMD_5032-2Pin_5.0x3.2mm; PartNumber X50328MSB2GI; LCSCStockCode C115962

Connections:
DUMP_LOAD_ENABLE: ATTINY841.5 (PB2), R14.2
ENABLE: ATTINY841.6 (PA7), R2.1, R3.1
GND: ATTINY841.14 (GND), C1.2, C2.2, C4.2, C5.2, D1.3 (A), D2.2 (A), POWER1.1, Q1.2 (S), R4.2, R15.2, R16.1, R18.1, R20.2, U1.2
MISO: ATTINY841.8 (PA5)
unnamed: ATTINY841.2 (XTAL1/PB0), C4.1, Y1.2
unnamed: ATTINY841.3 (XTAL2/PB1), C5.1, Y1.1
unnamed: ATTINY841.4 (~RESET/PB3), R1.2
unnamed: ATTINY841.7 (PA6), D4.2 (A)
unnamed: ATTINY841.10 (PA3), R3.2, R4.1
unnamed: D4.1 (K), R18.2
unnamed: F1.2, POWER1.2
unnamed: Q1.1 (G), R14.1, R15.1
unnamed: Q1.3 (D), R12.2, R29.2, R30.2, R31.2, R34.2, R37.2
unnamed: R5.1, U1.1
unnamed: R6.2, R8.1
unnamed: R8.2, R12.1
unnamed: R22.2, R25.1
unnamed: R24.2, R26.1
unnamed: R25.2, R29.1
unnamed: R26.2, R30.1
unnamed: R31.1, R32.2
unnamed: R32.1, R33.2
unnamed: R34.1, R35.2
unnamed: R35.1, R36.2
unnamed: R37.1, R38.2
unnamed: R38.1, R39.2
unnamed: TX1.1, U1.3
unnamed: TX1.2, U1.4
RXD0: ATTINY841.11 (PA2), R16.2, RX1.1
SCK: ATTINY841.9 (PA4), R19.2, R20.1
TXD0: ATTINY841.12 (PA1), R5.2
VCC: ATTINY841.1 (VCC), C1.1, C2.1, D2.1 (K), F1.1, R1.1, R6.1, R22.1, R24.1, R33.1, R36.1, R39.1, RX1.2
VREF: ATTINY841.13 (AREF/PA0), D1.1 (FB), D1.2 (K), R2.2, R19.1

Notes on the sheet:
UNIDIRECTIONAL 5V TVS
Internal temp sensor
CHIP RESISTOR - SURFACE MOUNT 3.3OHMS ±1% 3/4W 2010 ROHS, 3 in series with 3 in parallel gives 3.30 Ohm equivalent resistance 18 resistors provide 2*9*0.75W=13.5W of power disipation. Balance current (at 3.3ohm) (these calculations only use 9 resistors): 1.27A at 4.2V and 5.35W power 1.21A at 4.0V 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
mSMD150, 8V MAX, FUSE HOLD @ 1.5AMP, TRIP 3A
Diodes Incorporated VOLTAGE REFERENCES 1.25V ±0.5% 20PPM/°C
8Mhz used in CKDIV8 mode to power on at 1Mhz, code then swaps to 2Mhz using clock prescaler
NTC THERMISTORS 10KOHMS ±1% 3950K 0805 ROHS
ADC3=Output voltage 1.25V for input of 4.398V (max)
gate
Modified DIYBMS v4 CELL MONITORING MODULE VERSION 4.40 FOR LITHIUM VOLTAGE RANGES (18650 etc.) 0 - 4.2V
PA7 has a higher current output than other pins
source
4 PIN ULTRA SMALL SSOP PHOTOTRANSISTOR PHOTOCOUPLER EL3H7-G Series
MOSFET N TRENCH 30V 5.7A 1.5V @ 250UA 26.5 @ 5.7A 10V SOT-23-3L ROHS
drain

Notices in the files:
parts and their libraries:
Copyright 2021 Accelerated Designs. All rights reserved.
